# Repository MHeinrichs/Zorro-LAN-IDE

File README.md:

[This project moved to gitlab on the day M$ bought github](https://gitlab.com/MHeinrichs/Zorro-LAN-IDE)

The new repository is at: https://gitlab.com/MHeinrichs/Zorro-LAN-IDE

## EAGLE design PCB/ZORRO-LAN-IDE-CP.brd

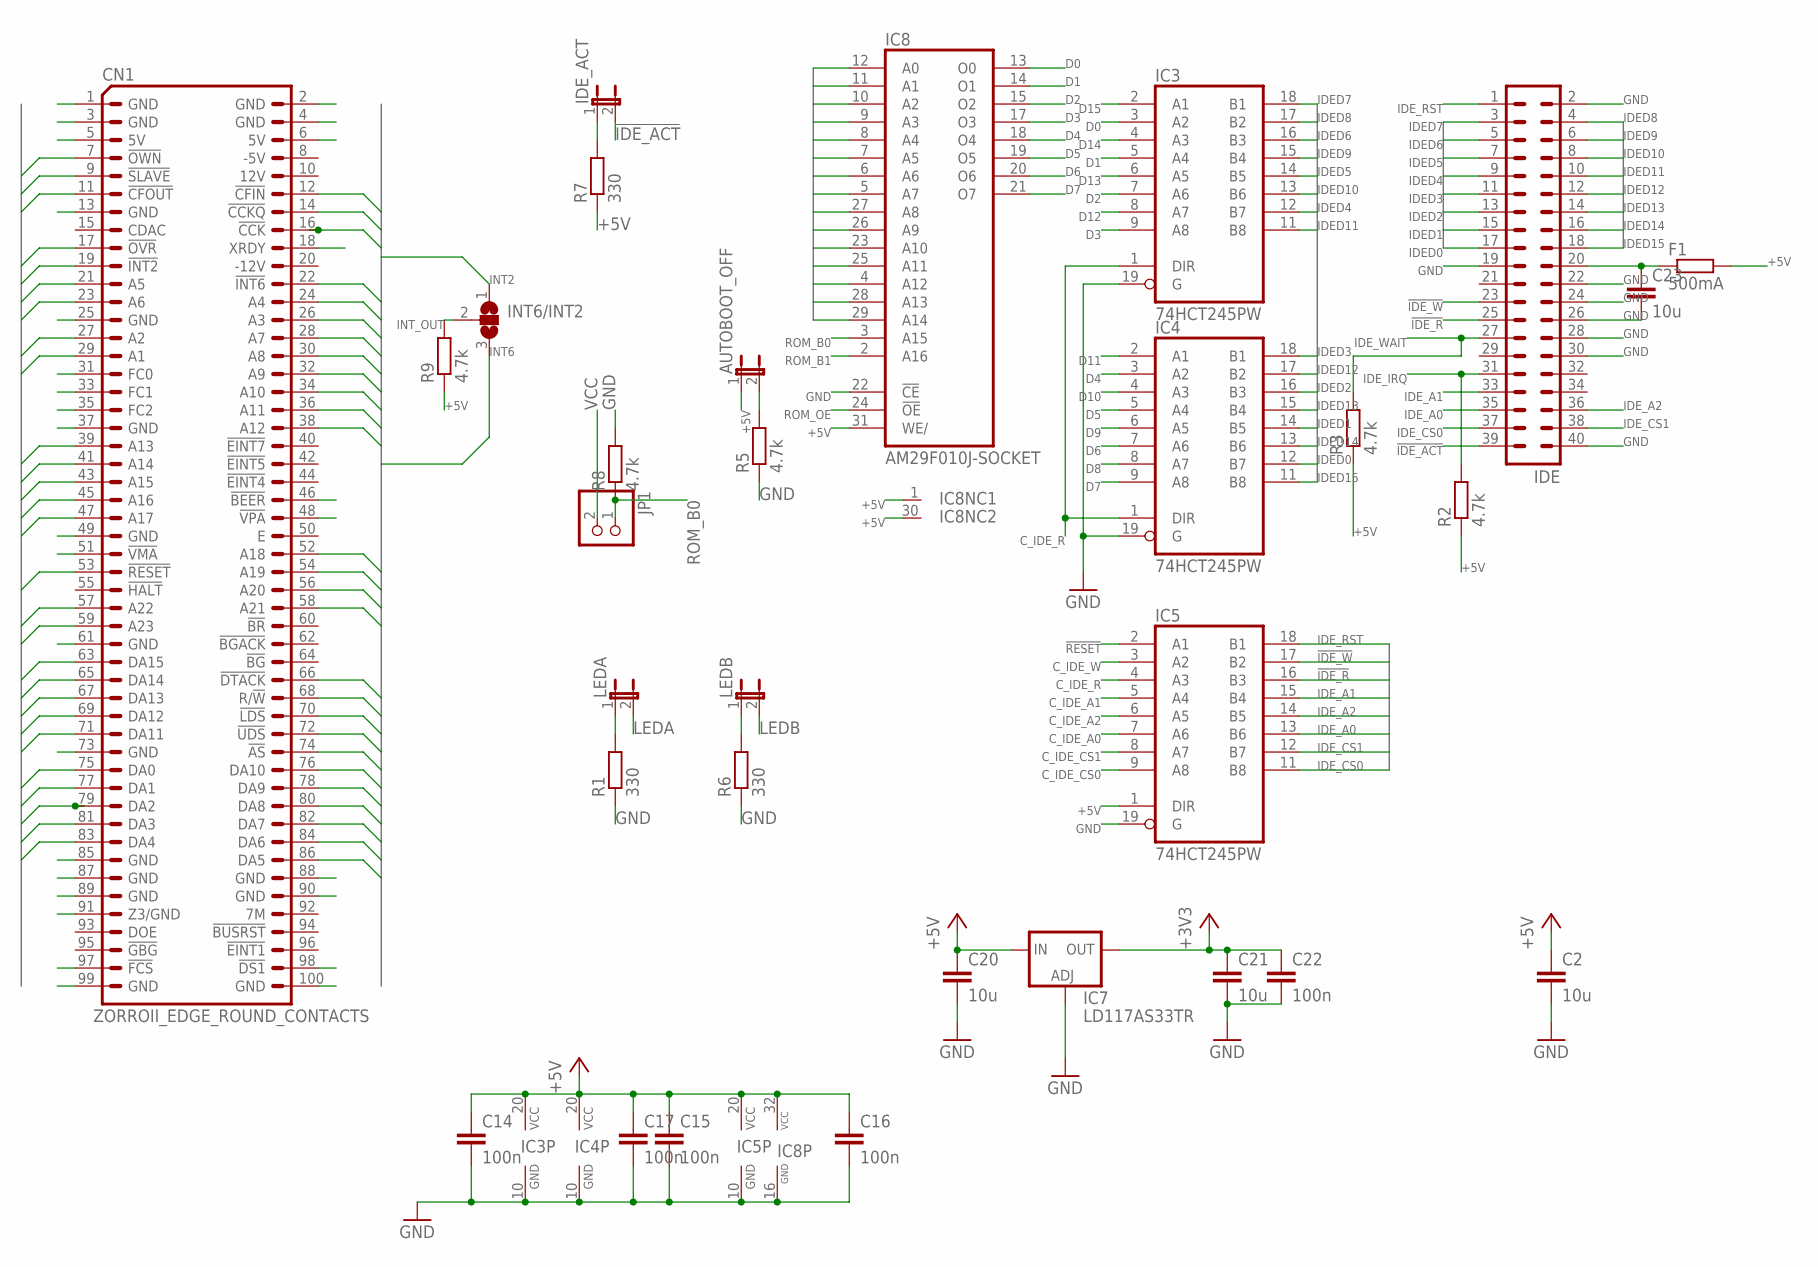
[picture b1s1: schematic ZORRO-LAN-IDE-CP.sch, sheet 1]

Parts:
AUTOBOOT_OFF: JP1E; JP1
C2, C20, C21, C23: 10u; C0805K
C14, C15, C16, C17, C22: 100n; C0603K
CN1: ZORROII_EDGE_ROUND_CONTACTS; LKONT_50_R
F1: 500mA; R2512
IC3, IC4, IC5: 74HCT245PW; TSSOP20
IC7: LD117AS33TR; SOT223
IC8: AM29F010J-SOCKET; PLCC-32-SMT-TT
IDE: ML40
IDE_ACT: JP1E; JP1
INT6/INT2: SJ2W; SJ_2
JP1: PINHD-1X02_2.54-S; 1X02-S
LEDA: JP1E; JP1
LEDB: JP1E; JP1
R1, R6, R7: 330; R0603
R2, R3, R5, R8, R9: 4.7k; R0603

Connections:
!AS: CN1.74 (!AS!); also elsewhere on the board
!BERR: CN1.46 (!BEER!); also elsewhere on the board
!CFIN: CN1.12 (!CFIN!); also elsewhere on the board
!CFOUT: CN1.11 (!CFOUT!); also elsewhere on the board
!DS0: CN1.51 (!VMA!); also elsewhere on the board
!DS1: CN1.98 (!DS1!); also elsewhere on the board
!DTACK: CN1.66 (!DTACK!); also elsewhere on the board
!FCS: CN1.97 (!FCS!); also elsewhere on the board
!IDE_ACT: IDE.39, IDE_ACT.2
!IDE_R: IC5.16 (B3), IDE.25
!IDE_W: IC5.17 (B2), IDE.23
!LDS: CN1.70 (!LDS!); also elsewhere on the board
!MTACK: CN1.48 (!VPA!); also elsewhere on the board
!MTCR: CN1.18 (XRDY); also elsewhere on the board
!OVR: CN1.17 (!OVR!); also elsewhere on the board
!OWN: CN1.7 (!OWN!); also elsewhere on the board
!RESET: CN1.53 (!RESET!), IC5.2 (A1); also elsewhere on the board
!SLAVE: CN1.9 (!SLAVE!); also elsewhere on the board
!UDS: CN1.72 (!UDS!); also elsewhere on the board
+3V3: C21.1, C22.1, IC7.2 (OUT), IC7.4 (OUT); also elsewhere on the board
+5V: AUTOBOOT_OFF.1, C2.1, C14.1, C15.1, C16.1, C17.1, C20.1, CN1.5 (5V), CN1.6 (5V), F1.2, IC3.20 (VCC), IC4.20 (VCC), IC5.1 (DIR), IC5.20 (VCC), IC7.3 (IN), IC8.1 (NC), IC8.30 (NC), IC8.31 (WE/), IC8.32 (VCC), R2.1, R3.1, R7.1, R9.1; also elsewhere on the board
A1: CN1.29 (A1), IC8.12 (A0); also elsewhere on the board
A2: CN1.27 (A2), IC8.11 (A1); also elsewhere on the board
A3: CN1.26 (A3), IC8.10 (A2); also elsewhere on the board
A4: CN1.24 (A4), IC8.9 (A3); also elsewhere on the board
A5: CN1.21 (A5), IC8.8 (A4); also elsewhere on the board
A6: CN1.23 (A6), IC8.7 (A5); also elsewhere on the board
A7: CN1.28 (A7), IC8.6 (A6); also elsewhere on the board
A8: CN1.30 (A8), IC8.5 (A7); also elsewhere on the board
A9: CN1.32 (A9), IC8.27 (A8); also elsewhere on the board
A10: CN1.34 (A10), IC8.26 (A9); also elsewhere on the board
A11: CN1.36 (A11), IC8.23 (A10); also elsewhere on the board
A12: CN1.38 (A12), IC8.25 (A11); also elsewhere on the board
A13: CN1.39 (A13), IC8.4 (A12); also elsewhere on the board
A14: CN1.41 (A14), IC8.28 (A13); also elsewhere on the board
A15: CN1.43 (A15), IC8.29 (A14); also elsewhere on the board
A16: CN1.45 (A16); also elsewhere on the board
A17: CN1.47 (A17); also elsewhere on the board
A18: CN1.52 (A18); also elsewhere on the board
A19: CN1.54 (A19); also elsewhere on the board
A20: CN1.56 (A20); also elsewhere on the board
A21: CN1.58 (A21); also elsewhere on the board
A22: CN1.57 (A22); also elsewhere on the board
A23: CN1.59 (A23); also elsewhere on the board
AUTO_BOOT_OFF: AUTOBOOT_OFF.2, R5.2; also elsewhere on the board
C1: CN1.14 (!CCKQ!); also elsewhere on the board
C3: CN1.16 (!CCK!); also elsewhere on the board
C_IDE_A0: IC5.7 (A6); also elsewhere on the board
C_IDE_A1: IC5.5 (A4); also elsewhere on the board
C_IDE_A2: IC5.6 (A5); also elsewhere on the board
C_IDE_CS0: IC5.9 (A8); also elsewhere on the board
C_IDE_CS1: IC5.8 (A7); also elsewhere on the board
C_IDE_R: IC3.1 (DIR), IC4.1 (DIR), IC5.4 (A3); also elsewhere on the board
C_IDE_W: IC5.3 (A2); also elsewhere on the board
D0: CN1.75 (DA0), IC3.3 (A2), IC8.13 (O0); also elsewhere on the board
D1: CN1.77 (DA1), IC3.5 (A4), IC8.14 (O1); also elsewhere on the board
D2: CN1.79 (DA2), IC3.7 (A6), IC8.15 (O2); also elsewhere on the board
D3: CN1.81 (DA3), IC3.9 (A8), IC8.17 (O3); also elsewhere on the board
D4: CN1.83 (DA4), IC4.3 (A2), IC8.18 (O4); also elsewhere on the board
D5: CN1.86 (DA5), IC4.5 (A4), IC8.19 (O5); also elsewhere on the board
D6: CN1.84 (DA6), IC4.7 (A6), IC8.20 (O6); also elsewhere on the board
D7: CN1.82 (DA7), IC4.9 (A8), IC8.21 (O7); also elsewhere on the board
D8: CN1.80 (DA8), IC4.8 (A7); also elsewhere on the board
D9: CN1.78 (DA9), IC4.6 (A5); also elsewhere on the board
D10: CN1.76 (DA10), IC4.4 (A3); also elsewhere on the board
D11: CN1.71 (DA11), IC4.2 (A1); also elsewhere on the board
D12: CN1.69 (DA12), IC3.8 (A7); also elsewhere on the board
D13: CN1.67 (DA13), IC3.6 (A5); also elsewhere on the board
D14: CN1.65 (DA14), IC3.4 (A3); also elsewhere on the board
D15: CN1.63 (DA15), IC3.2 (A1); also elsewhere on the board
FC0: CN1.31 (FC0)
FC1: CN1.33 (FC1)
FC2: CN1.35 (FC2)
GND: C2.2, C14.2, C15.2, C16.2, C17.2, C20.2, C21.2, C22.2, C23.2, CN1.1 (GND), CN1.2 (GND), CN1.3 (GND), CN1.4 (GND), CN1.13 (GND), CN1.25 (GND), CN1.37 (GND), CN1.49 (GND), CN1.61 (GND), CN1.73 (GND), CN1.85 (GND), CN1.87 (GND), CN1.88 (GND), CN1.89 (GND), CN1.90 (GND), CN1.99 (GND), CN1.100 (GND), IC3.10 (GND), IC3.19 (G), IC4.10 (GND), IC4.19 (G), IC5.10 (GND), IC5.19 (G), IC7.1 (ADJ), IC8.16 (GND), IC8.22 (!CE), IDE.2, IDE.19, IDE.22, IDE.24, IDE.26, IDE.28, IDE.30, IDE.40, R1.1, R5.1, R6.1, R8.2; also elsewhere on the board
IDED0: IC4.12 (B7), IDE.17
IDED1: IC4.14 (B5), IDE.15
IDED2: IC4.16 (B3), IDE.13
IDED3: IC4.18 (B1), IDE.11
IDED4: IC3.12 (B7), IDE.9
IDED5: IC3.14 (B5), IDE.7
IDED6: IC3.16 (B3), IDE.5
IDED7: IC3.18 (B1), IDE.3
IDED8: IC3.17 (B2), IDE.4
IDED9: IC3.15 (B4), IDE.6
IDED10: IC3.13 (B6), IDE.8
IDED11: IC3.11 (B8), IDE.10
IDED12: IC4.17 (B2), IDE.12
IDED13: IC4.15 (B4), IDE.14
IDED14: IC4.13 (B6), IDE.16
IDED15: IC4.11 (B8), IDE.18
IDE_A0: IC5.13 (B6), IDE.35
IDE_A1: IC5.15 (B4), IDE.33
IDE_A2: IC5.14 (B5), IDE.36
IDE_CS0: IC5.11 (B8), IDE.37
IDE_CS1: IC5.12 (B7), IDE.38
IDE_IRQ: IDE.31, R2.2
IDE_RST: IC5.18 (B1), IDE.1; also elsewhere on the board
IDE_WAIT: IDE.27, R3.2; also elsewhere on the board
INT2: CN1.19 (!INT2!), INT6/INT2.1
INT6: CN1.22 (!INT6!), INT6/INT2.3
INT_OUT: INT6/INT2.2, R9.2; also elsewhere on the board
KEY_PIN_POWER: C23.1, F1.1, IDE.20
LEDA: LEDA.2; also elsewhere on the board
LEDB: LEDB.2; also elsewhere on the board
unnamed: LEDA.1, R1.2
unnamed: LEDB.1, R6.2
unnamed: IDE_ACT.1, R7.2
R/W: CN1.68 (R/!W!); also elsewhere on the board
ROM_B0: IC8.3 (A15), JP1.1, R8.1; also elsewhere on the board
ROM_B1: IC8.2 (A16); also elsewhere on the board
ROM_OE: IC8.24 (!OE); also elsewhere on the board
VCC: JP1.2
Z3: CN1.91 (Z3/GND); also elsewhere on the board

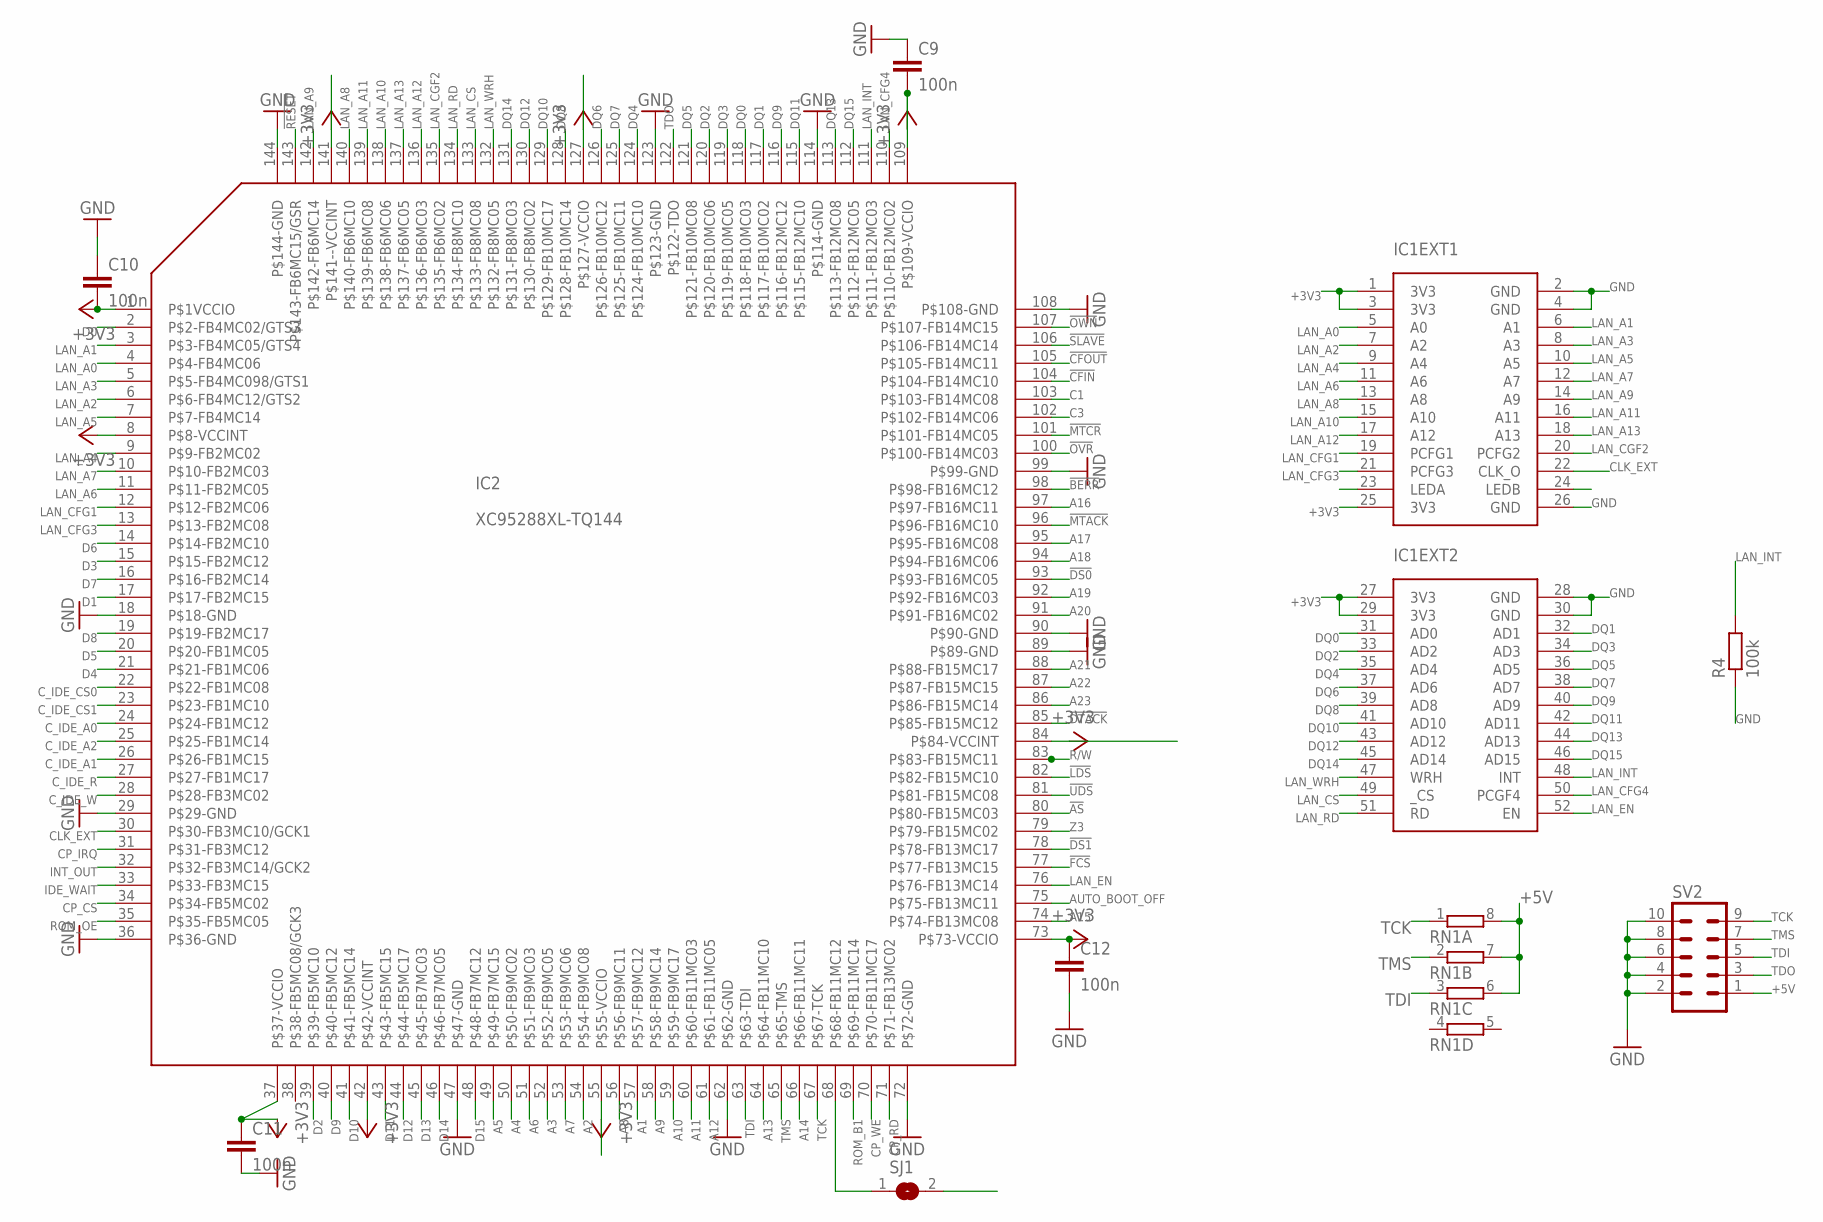
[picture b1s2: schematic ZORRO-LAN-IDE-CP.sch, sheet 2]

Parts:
C9, C10, C11, C12: 100n; C0603K
IC1: OLIMEX_ENC; OLIMEX-ENC624J600
IC2: XC95288XL-TQ144; TQFP144
R4: 100k; R0603
RN1: 4R-NCAY16; CAY16
SJ1: SJ
SV2: ML10L

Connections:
!AS: IC2.80 (P$80-FB15MC03); also elsewhere on the board
!BERR: IC2.98 (P$98-FB16MC12); also elsewhere on the board
!CFIN: IC2.104 (P$104-FB14MC10); also elsewhere on the board
!CFOUT: IC2.105 (P$105-FB14MC11); also elsewhere on the board
!DS0: IC2.93 (P$93-FB16MC05); also elsewhere on the board
!DS1: IC2.78 (P$78-FB13MC17); also elsewhere on the board
!DTACK: IC2.85 (P$85-FB15MC12); also elsewhere on the board
!FCS: IC2.77 (P$77-FB13MC15); also elsewhere on the board
!LDS: IC2.82 (P$82-FB15MC10); also elsewhere on the board
!MTACK: IC2.96 (P$96-FB16MC10); also elsewhere on the board
!MTCR: IC2.101 (P$101-FB14MC05); also elsewhere on the board
!OVR: IC2.100 (P$100-FB14MC03); also elsewhere on the board
!OWN: IC2.107 (P$107-FB14MC15); also elsewhere on the board
!RESET: IC2.143 (P$143-FB6MC15/GSR); also elsewhere on the board
!SLAVE: IC2.106 (P$106-FB14MC14); also elsewhere on the board
!UDS: IC2.81 (P$81-FB15MC08); also elsewhere on the board
+3V3: C9.2, C10.2, C11.1, C12.1, IC1.1 (3V3), IC1.3 (3V3), IC1.25 (3V3), IC1.27 (3V3), IC1.29 (3V3), IC2.1 (P$1VCCIO), IC2.8 (P$8-VCCINT), IC2.37 (P$37-VCCIO), IC2.42 (P$42-VCCINT), IC2.55 (P$55-VCCIO), IC2.73 (P$73-VCCIO), IC2.84 (P$84-VCCINT), IC2.109 (P$109-VCCIO), IC2.127 (P$127-VCCIO), IC2.141 (P$141--VCCINT); also elsewhere on the board
+5V: RN1.6 (2), RN1.7 (2), RN1.8 (2), SV2.1; also elsewhere on the board
A1: IC2.57 (P$57-FB9MC12); also elsewhere on the board
A2: IC2.54 (P$54-FB9MC08); also elsewhere on the board
A3: IC2.52 (P$52-FB9MC05); also elsewhere on the board
A4: IC2.50 (P$50-FB9MC02); also elsewhere on the board
A5: IC2.49 (P$49-FB7MC15); also elsewhere on the board
A6: IC2.51 (P$51-FB9MC03); also elsewhere on the board
A7: IC2.53 (P$53-FB9MC06); also elsewhere on the board
A8: IC2.56 (P$56-FB9MC11); also elsewhere on the board
A9: IC2.58 (P$58-FB9MC14); also elsewhere on the board
A10: IC2.59 (P$59-FB9MC17); also elsewhere on the board
A11: IC2.60 (P$60-FB11MC03); also elsewhere on the board
A12: IC2.61 (P$61-FB11MC05); also elsewhere on the board
A13: IC2.64 (P$64-FB11MC10); also elsewhere on the board
A14: IC2.66 (P$66-FB11MC11); also elsewhere on the board
A15: IC2.74 (P$74-FB13MC08); also elsewhere on the board
A16: IC2.97 (P$97-FB16MC11); also elsewhere on the board
A17: IC2.95 (P$95-FB16MC08); also elsewhere on the board
A18: IC2.94 (P$94-FB16MC06); also elsewhere on the board
A19: IC2.92 (P$92-FB16MC03); also elsewhere on the board
A20: IC2.91 (P$91-FB16MC02); also elsewhere on the board
A21: IC2.88 (P$88-FB15MC17); also elsewhere on the board
A22: IC2.87 (P$87-FB15MC15); also elsewhere on the board
A23: IC2.86 (P$86-FB15MC14); also elsewhere on the board
AUTO_BOOT_OFF: IC2.75 (P$75-FB13MC11); also elsewhere on the board
C1: IC2.103 (P$103-FB14MC08); also elsewhere on the board
C3: IC2.102 (P$102-FB14MC06); also elsewhere on the board
CLK_EXT: IC1.22 (CLK_O), IC2.30 (P$30-FB3MC10/GCK1)
CP_CS: IC2.34 (P$34-FB5MC02); also elsewhere on the board
CP_IRQ: IC2.31 (P$31-FB3MC12); also elsewhere on the board
CP_RD: IC2.71 (P$71-FB13MC02); also elsewhere on the board
CP_WE: IC2.70 (P$70-FB11MC17); also elsewhere on the board
C_IDE_A0: IC2.24 (P$24-FB1MC12); also elsewhere on the board
C_IDE_A1: IC2.26 (P$26-FB1MC15); also elsewhere on the board
C_IDE_A2: IC2.25 (P$25-FB1MC14); also elsewhere on the board
C_IDE_CS0: IC2.22 (P$22-FB1MC08); also elsewhere on the board
C_IDE_CS1: IC2.23 (P$23-FB1MC10); also elsewhere on the board
C_IDE_R: IC2.27 (P$27-FB1MC17); also elsewhere on the board
C_IDE_W: IC2.28 (P$28-FB3MC02); also elsewhere on the board
D0: IC2.2 (P$2-FB4MC02/GTS3); also elsewhere on the board
D1: IC2.17 (P$17-FB2MC15); also elsewhere on the board
D2: IC2.39 (P$39-FB5MC10); also elsewhere on the board
D3: IC2.15 (P$15-FB2MC12); also elsewhere on the board
D4: IC2.21 (P$21-FB1MC06); also elsewhere on the board
D5: IC2.20 (P$20-FB1MC05); also elsewhere on the board
D6: IC2.14 (P$14-FB2MC10); also elsewhere on the board
D7: IC2.16 (P$16-FB2MC14); also elsewhere on the board
D8: IC2.19 (P$19-FB2MC17); also elsewhere on the board
D9: IC2.40 (P$40-FB5MC12); also elsewhere on the board
D10: IC2.41 (P$41-FB5MC14); also elsewhere on the board
D11: IC2.43 (P$43-FB5MC15); also elsewhere on the board
D12: IC2.44 (P$44-FB5MC17); also elsewhere on the board
D13: IC2.45 (P$45-FB7MC03); also elsewhere on the board
D14: IC2.46 (P$46-FB7MC05); also elsewhere on the board
D15: IC2.48 (P$48-FB7MC12); also elsewhere on the board
DQ0: IC1.31 (AD0), IC2.118 (P$118-FB10MC03); also elsewhere on the board
DQ1: IC1.32 (AD1), IC2.117 (P$117-FB10MC02); also elsewhere on the board
DQ2: IC1.33 (AD2), IC2.120 (P$120-FB10MC06); also elsewhere on the board
DQ3: IC1.34 (AD3), IC2.119 (P$119-FB10MC05); also elsewhere on the board
DQ4: IC1.35 (AD4), IC2.124 (P$124-FB10MC10); also elsewhere on the board
DQ5: IC1.36 (AD5), IC2.121 (P$121-FB10MC08); also elsewhere on the board
DQ6: IC1.37 (AD6), IC2.126 (P$126-FB10MC12); also elsewhere on the board
DQ7: IC1.38 (AD7), IC2.125 (P$125-FB10MC11); also elsewhere on the board
DQ8: IC1.39 (AD8), IC2.128 (P$128-FB10MC14)
DQ9: IC1.40 (AD9), IC2.116 (P$116-FB12MC12)
DQ10: IC1.41 (AD10), IC2.129 (P$129-FB10MC17)
DQ11: IC1.42 (AD11), IC2.115 (P$115-FB12MC10)
DQ12: IC1.43 (AD12), IC2.130 (P$130-FB8MC02)
DQ13: IC1.44 (AD13), IC2.113 (P$113-FB12MC08)
DQ14: IC1.45 (AD14), IC2.131 (P$131-FB8MC03)
DQ15: IC1.46 (AD15), IC2.112 (P$112-FB12MC05)
GND: C9.1, C10.1, C11.2, C12.2, IC1.2 (GND), IC1.4 (GND), IC1.26 (GND), IC1.28 (GND), IC1.30 (GND), IC2.18 (P$18-GND), IC2.29 (P$29-GND), IC2.36 (P$36-GND), IC2.47 (P$47-GND), IC2.62 (P$62-GND), IC2.72 (P$72-GND), IC2.89 (P$89-GND), IC2.90 (P$90-GND), IC2.99 (P$99-GND), IC2.108 (P$108-GND), IC2.114 (P$114-GND), IC2.123 (P$123-GND), IC2.144 (P$144-GND), R4.1, SV2.2, SV2.4, SV2.6, SV2.8, SV2.10; also elsewhere on the board
IDE_WAIT: IC2.33 (P$33-FB3MC15); also elsewhere on the board
INT_OUT: IC2.32 (P$32-FB3MC14/GCK2); also elsewhere on the board
LAN_A0: IC1.5 (A0), IC2.4 (P$4-FB4MC06)
LAN_A1: IC1.6 (A1), IC2.3 (P$3-FB4MC05/GTS4)
LAN_A2: IC1.7 (A2), IC2.6 (P$6-FB4MC12/GTS2); also elsewhere on the board
LAN_A3: IC1.8 (A3), IC2.5 (P$5-FB4MC098/GTS1); also elsewhere on the board
LAN_A4: IC1.9 (A4), IC2.9 (P$9-FB2MC02); also elsewhere on the board
LAN_A5: IC1.10 (A5), IC2.7 (P$7-FB4MC14); also elsewhere on the board
LAN_A6: IC1.11 (A6), IC2.11 (P$11-FB2MC05)
LAN_A7: IC1.12 (A7), IC2.10 (P$10-FB2MC03)
LAN_A8: IC1.13 (A8), IC2.140 (P$140-FB6MC10)
LAN_A9: IC1.14 (A9), IC2.142 (P$142-FB6MC14)
LAN_A10: IC1.15 (A10), IC2.138 (P$138-FB6MC06)
LAN_A11: IC1.16 (A11), IC2.139 (P$139-FB6MC08)
LAN_A12: IC1.17 (A12), IC2.136 (P$136-FB6MC03)
LAN_A13: IC1.18 (A13), IC2.137 (P$137-FB6MC05)
LAN_CFG1: IC1.19 (PCFG1), IC2.12 (P$12-FB2MC06)
LAN_CFG3: IC1.21 (PCFG3), IC2.13 (P$13-FB2MC08)
LAN_CFG4: IC1.50 (PCGF4), IC2.110 (P$110-FB12MC02)
LAN_CGF2: IC1.20 (PCFG2), IC2.135 (P$135-FB6MC02)
LAN_CS: IC1.49 (_CS), IC2.133 (P$133-FB8MC08)
LAN_EN: IC1.52 (EN), IC2.76 (P$76-FB13MC14)
LAN_INT: IC1.48 (INT), IC2.111 (P$111-FB12MC03), R4.2
LAN_RD: IC1.51 (RD), IC2.134 (P$134-FB8MC10)
LAN_WRH: IC1.47 (WRH), IC2.132 (P$132-FB8MC05)
LEDA: IC1.23 (LEDA); also elsewhere on the board
LEDB: IC1.24 (LEDB); also elsewhere on the board
unnamed: IC2.68 (P$68-FB11MC12), SJ1.1
R/W: IC2.83 (P$83-FB15MC11); also elsewhere on the board
ROM_B0: SJ1.2; also elsewhere on the board
ROM_B1: IC2.69 (P$69-FB11MC14); also elsewhere on the board
ROM_OE: IC2.35 (P$35-FB5MC05); also elsewhere on the board
TCK: IC2.67 (P$67-TCK), RN1.1, SV2.9
TDI: IC2.63 (P$63-TDI), RN1.3 (1), SV2.5
TDO: IC2.122 (P$122-TDO), SV2.3
TMS: IC2.65 (P$65-TMS), RN1.2 (1), SV2.7
Z3: IC2.79 (P$79-FB15MC02); also elsewhere on the board

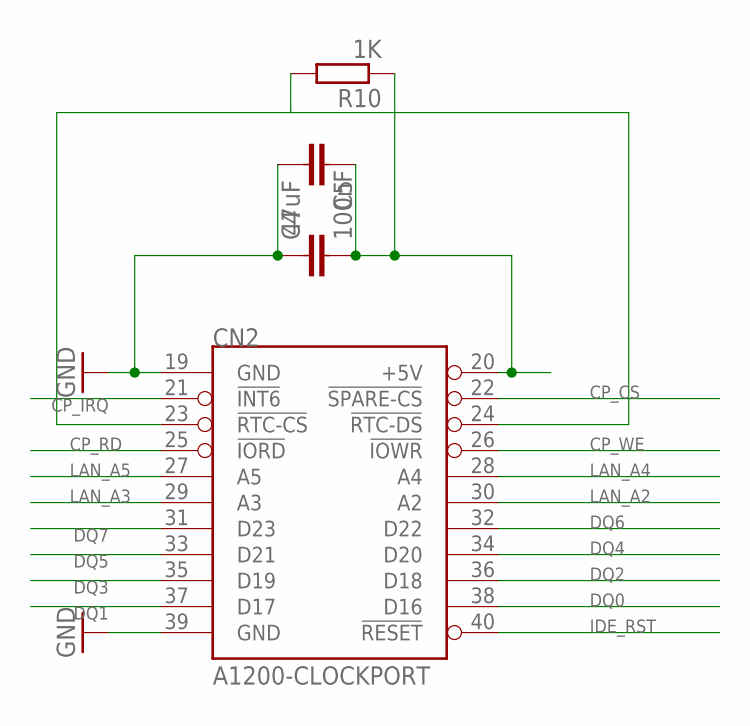
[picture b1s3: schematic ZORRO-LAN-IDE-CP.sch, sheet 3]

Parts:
C4: 100nF; C0805K
C5: 47uF; C1206K
CN2: A1200-CLOCKPORT; CP-2X11-2.00
R10: 1K; R0805

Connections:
+5V: C4.2, C5.1, CN2.20 (+5V), R10.1; also elsewhere on the board
CP_CS: CN2.22 (!SPARE-CS); also elsewhere on the board
CP_IRQ: CN2.21 (!INT6); also elsewhere on the board
CP_RD: CN2.25 (!IORD); also elsewhere on the board
CP_WE: CN2.26 (!IOWR); also elsewhere on the board
DQ0: CN2.38 (D16); also elsewhere on the board
DQ1: CN2.37 (D17); also elsewhere on the board
DQ2: CN2.36 (D18); also elsewhere on the board
DQ3: CN2.35 (D19); also elsewhere on the board
DQ4: CN2.34 (D20); also elsewhere on the board
DQ5: CN2.33 (D21); also elsewhere on the board
DQ6: CN2.32 (D22); also elsewhere on the board
DQ7: CN2.31 (D23); also elsewhere on the board
GND: C4.1, C5.2, CN2.19 (GND), CN2.39 (GND); also elsewhere on the board
IDE_RST: CN2.40 (!RESET); also elsewhere on the board
LAN_A2: CN2.30 (A2); also elsewhere on the board
LAN_A3: CN2.29 (A3); also elsewhere on the board
LAN_A4: CN2.28 (A4); also elsewhere on the board
LAN_A5: CN2.27 (A5); also elsewhere on the board
unnamed: CN2.23 (!RTC-CS), CN2.24 (!RTC-DS), R10.2

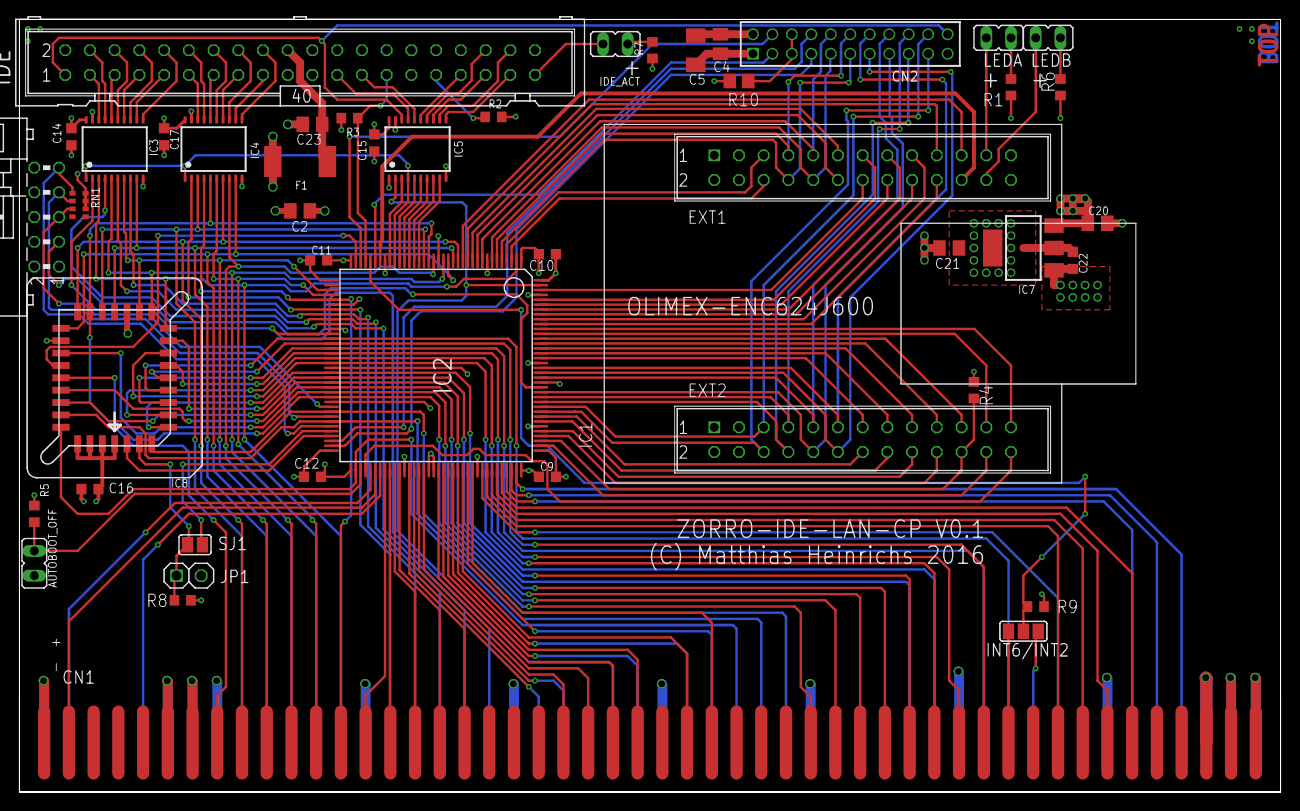
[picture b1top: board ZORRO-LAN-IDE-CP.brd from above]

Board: 4 copper layers, 129.5 x 79.4 mm, 45 parts (0 on the bottom side), 159 nets.

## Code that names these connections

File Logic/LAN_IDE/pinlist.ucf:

#PACE: Start of Constraints generated by PACE
#PACE: Start of PACE I/O Pin Assignments
NET "A<10>"  LOC = "P59"  ; 
NET "A<11>"  LOC = "P60"  ; 
NET "A<12>"  LOC = "P61"  ; 
NET "A<13>"  LOC = "P64"  ; 
NET "A<14>"  LOC = "P66"  ; 
NET "A<15>"  LOC = "P74"  ; 
NET "A<16>"  LOC = "P97"  ; 
NET "A<17>"  LOC = "P95"  ; 
NET "A<18>"  LOC = "P94"  ; 
NET "A<19>"  LOC = "P92"  ; 
NET "A<1>"  LOC = "P57"  ; 
NET "A<20>"  LOC = "P91"  ; 
NET "A<21>"  LOC = "P88"  ; 
NET "A<22>"  LOC = "P87"  ; 
NET "A<23>"  LOC = "P86"  ; 
NET "A<2>"  LOC = "P54"  ; 
NET "A<3>"  LOC = "P52"  ; 
NET "A<4>"  LOC = "P50"  ; 
NET "A<5>"  LOC = "P49"  ; 
NET "A<6>"  LOC = "P51"  ; 
NET "A<7>"  LOC = "P53"  ; 
NET "A<8>"  LOC = "P56"  ; 
NET "A<9>"  LOC = "P58"  ; 
NET "A_LAN<0>"  LOC = "P4"  ;
NET "A_LAN<10>"  LOC = "P138"  ;
NET "A_LAN<11>"  LOC = "P139"  ;
NET "A_LAN<12>"  LOC = "P136"  ;
NET "A_LAN<13>"  LOC = "P137"  ;
NET "A_LAN<1>"  LOC = "P3"  ;
NET "A_LAN<2>"  LOC = "P6"  ;
NET "A_LAN<3>"  LOC = "P5"  ;
NET "A_LAN<4>"  LOC = "P9"  ;
NET "A_LAN<5>"  LOC = "P7"  ;
NET "A_LAN<6>"  LOC = "P11"  ;
NET "A_LAN<7>"  LOC = "P10"  ;
NET "A_LAN<8>"  LOC = "P140"  ;
NET "A_LAN<9>"  LOC = "P142"  ;
NET "AS"  LOC = "P80"  ; 
NET "AUTOBOOT_OFF"  LOC = "P75"  ; 
NET "BERR"  LOC = "P98"  ; 
NET "C1"  LOC = "P103"  ; 
NET "C3"  LOC = "P102"  ; 
NET "CFIN"  LOC = "P104"  ; 
NET "CFOUT"  LOC = "P105"  ; 
NET "CLK_EXT"  LOC = "P30"  ;
NET "CP_CS"  LOC = "P34"  ;
NET "CP_IRQ"  LOC = "P31"  ;
NET "CP_RD"  LOC = "P71"  ;
NET "CP_WE"  LOC = "P70"  ;
NET "D<0>"  LOC = "P2"  ; 
NET "D<10>"  LOC = "P41"  ; 
NET "D<11>"  LOC = "P43"  ; 
NET "D<12>"  LOC = "P44"  ; 
NET "D<13>"  LOC = "P45"  ; 
NET "D<14>"  LOC = "P46"  ; 
NET "D<15>"  LOC = "P48"  ; 
NET "D<1>"  LOC = "P17"  ; 
NET "D<2>"  LOC = "P39"  ; 
NET "D<3>"  LOC = "P15"  ; 
NET "D<4>"  LOC = "P21"  ; 
NET "D<5>"  LOC = "P20"  ; 
NET "D<6>"  LOC = "P14"  ; 
NET "D<7>"  LOC = "P16"  ; 
NET "D<8>"  LOC = "P19"  ; 
NET "D<9>"  LOC = "P40"  ; 
NET "DQ<0>"  LOC = "P118"  ;
NET "DQ<10>"  LOC = "P129"  ;
NET "DQ<11>"  LOC = "P115"  ;
NET "DQ<12>"  LOC = "P130"  ;
NET "DQ<13>"  LOC = "P113"  ;
NET "DQ<14>"  LOC = "P131"  ;
NET "DQ<15>"  LOC = "P112"  ;
NET "DQ<1>"  LOC = "P117"  ;
NET "DQ<2>"  LOC = "P120"  ;
//NET "DQ<2>"  LOC = "P68"  ; //fix for broken Xilinx
NET "DQ<3>"  LOC = "P119"  ;
NET "DQ<4>"  LOC = "P124"  ;
NET "DQ<5>"  LOC = "P121"  ;
//NET "DQ<5>"  LOC = "P38"  ;//fix for broken Xilinx
NET "DQ<6>"  LOC = "P126"  ;
NET "DQ<7>"  LOC = "P125"  ;
NET "DQ<8>"  LOC = "P128"  ;
NET "DQ<9>"  LOC = "P116"  ;
NET "DS0"  LOC = "P93"  ; 
NET "DS1"  LOC = "P78"  ; 
NET "DTACK"  LOC = "P85"  ; 
NET "FCS"  LOC = "P77"  ; 
NET "IDE_A<0>"  LOC = "P24"  ;
NET "IDE_A<1>"  LOC = "P26"  ;
NET "IDE_A<2>"  LOC = "P25"  ;
NET "IDE_CS<0>"  LOC = "P22"  ;
NET "IDE_CS<1>"  LOC = "P23"  ;
NET "IDE_R"  LOC = "P27"  ;
NET "IDE_W"  LOC = "P28"  ;
NET "IDE_WAIT"  LOC = "P33"  ;
NET "INT_OUT"  LOC = "P32"  ;
NET "LAN_CFG<1>"  LOC = "P12"  ;
NET "LAN_CFG<2>"  LOC = "P135"  ;
NET "LAN_CFG<3>"  LOC = "P13"  ;
NET "LAN_CFG<4>"  LOC = "P110"  ;
NET "LAN_CS"  LOC = "P133"  ;
NET "LAN_WRL"  LOC = "P76"  ; 
NET "LAN_INT"  LOC = "P111"  ;
NET "LAN_RD"  LOC = "P134"  ;
NET "LAN_WRH"  LOC = "P132"  ;
NET "LDS"  LOC = "P82"  ; 
NET "MTACK"  LOC = "P96"  ; 
NET "MTCR"  LOC = "P101"  ; 
NET "OVR"  LOC = "P100"  ; 
NET "OWN"  LOC = "P107"  ; 
NET "RESET"  LOC = "P143"  ;
NET "ROM_B<0>"  LOC = "P68"  ;//comment if fix for broken Xilinx!
NET "ROM_B<1>"  LOC = "P69"  ;
NET "ROM_OE"  LOC = "P35"  ;
NET "RW"  LOC = "P83"  ;
NET "SLAVE"  LOC = "P106"  ; 
NET "UDS"  LOC = "P81"  ; 
NET "Z3"  LOC = "P79"  ;
#Created by Constraints Editor (xc95288xl-tq144-10) - 2017/01/26
NET "CLK_EXT" TNM_NET = CLK_EXT;
TIMESPEC TS_CLK_EXT = PERIOD "CLK_EXT" 33 MHz HIGH 50%;
NET "C1" TNM_NET = C1;
TIMESPEC TS_C1 = PERIOD "C1" 3.5 MHz HIGH 50%;
NET "C3" TNM_NET = C3;
TIMESPEC TS_C3 = PERIOD "C3" 3.5 MHz HIGH 50%;

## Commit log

2016-12-13 :circus_tent: Added .gitattributes & .gitignore files
2016-12-13 Initial push
2016-12-14 Structure ready
2016-12-15 IDE & Autoconfig working
2016-12-15 Autocnfig working
2016-12-15 compiled
2016-12-15 Now the interface mmust be initialized and tested
2016-12-15 programming file added
2016-12-28 Starting the init routiune
2016-12-28 Setting the clock
2016-12-28 to much logic!
2016-12-28 new style of autoconfig
2016-12-28 new style of autoconfig 2
2016-12-28 Got it?!?
2016-12-29 ac working
2017-01-07 Where is the bug?
2017-01-07 AC very smart&slim but its not working! WHY????
2017-01-14 Still no success
2017-01-15 Testbench added
2017-01-18 fixcing the init-routines!
2017-01-18 InitLan works and macros put in the ENCX24J-Lib
2017-01-18 Better functions to InitLAN
2017-01-18 Fixed an error in the debug-output and switched to "faulty xilinx"-pinout
2017-01-26 Reset in hardware and clock set to 33mhz
2017-01-26 OK Clock is 33MHz but the timing to AmigaCLK cannot be convertet 1:1...
2017-01-27 CP timing fixed and Bytemirror for CP
2017-12-20 ENC264J600 driver - initial prototype, based on Plipbox framework - handles some oddities with the current CPLD by software workarounds, i.e. needs future changes to go along with updated JED - lots 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
2017-12-20 added two pictures
2017-12-21 Address-Swap for A13/12 and Byteswap from $6000-$7FFF
2017-12-22 PCB/Fixes.txt - Hinweise zu den Prototypen cp-fix.jpg - ClockPort Interrupt fix im Bild
2017-12-22 LAN-INT-Disable implemented
2017-12-22 Cleaned up firmware
2017-12-24 ENC624j6net - updated source to match the JED from 22Dec2017 - now interrupt support is enabled in driver - ping times improved considerably
2017-12-26 Byteswap disabled
2017-12-27 - Driver optimization
2018-01-09 ENC624J6Net - changed interrupt usage for Int2 instead of Int6 (after discussion with Matze about "best" approach) - see HW_INTSOURCE in hw.c for the active interrupt source - this build reflects cha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
2018-01-21 first hit for public
2018-01-21 License Added
2018-01-22 License must be GNU due to use of Plipbox
2018-01-24 Added IDE-Disable option
2018-02-01 Fixed Autoconfig-Bug, improved interrupthandling multiple package support
2018-02-01 Driver - removed object files from svn (screwed up diffs) - set svn mime type to binary for .device and assembler - reverted list handling in server.c doreadreqs()
2018-02-03 A12/13 fix Driver improvement git-ignore cleaned
2018-02-05 alignment bug fixed and asm routines splitted
    Revertet server.c to a stable version
2018-02-08 Tweaked the driver a bit
2018-04-16 LAN Driver - bugfix: wraparound aware RX routine was potentially over- or undershooting by two bytes - slight improvement to RX loop - revision bump to 0.2
2018-04-25 enc624j6net - improved duplex/offline check handling - better TX handling (one less full frame copy per TX request), i.e. direct write from driver to HW buffer - some other minor changes - revised TX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
2018-04-30 Logic update - fix LAN port byte swap with byte writes - swap UDS/LDS mapping to WRL/WRL - duplicate LAN DQ bytes by re-using ClockPort logic - issues: - DQ logic doesn't fit in one Function Block an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
2019-08-28 Moved to gitlab
